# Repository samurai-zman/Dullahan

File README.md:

# Dullahan
A portable "Headless" modular multiport multitool, designed to emphasize adaptability for electronic measurements.

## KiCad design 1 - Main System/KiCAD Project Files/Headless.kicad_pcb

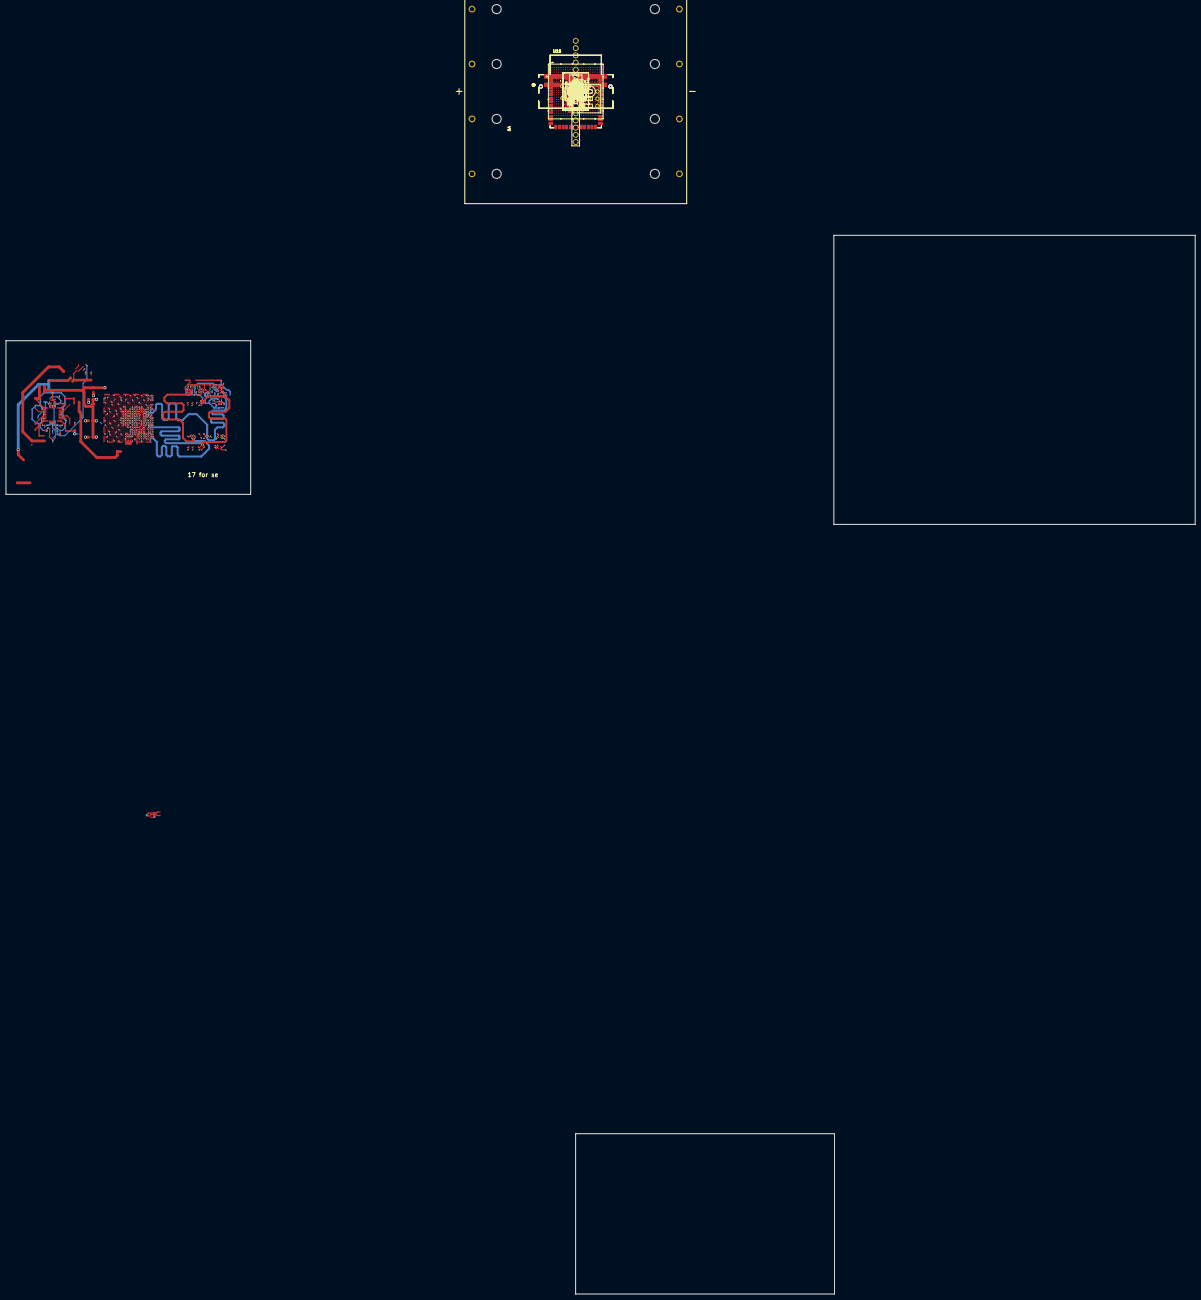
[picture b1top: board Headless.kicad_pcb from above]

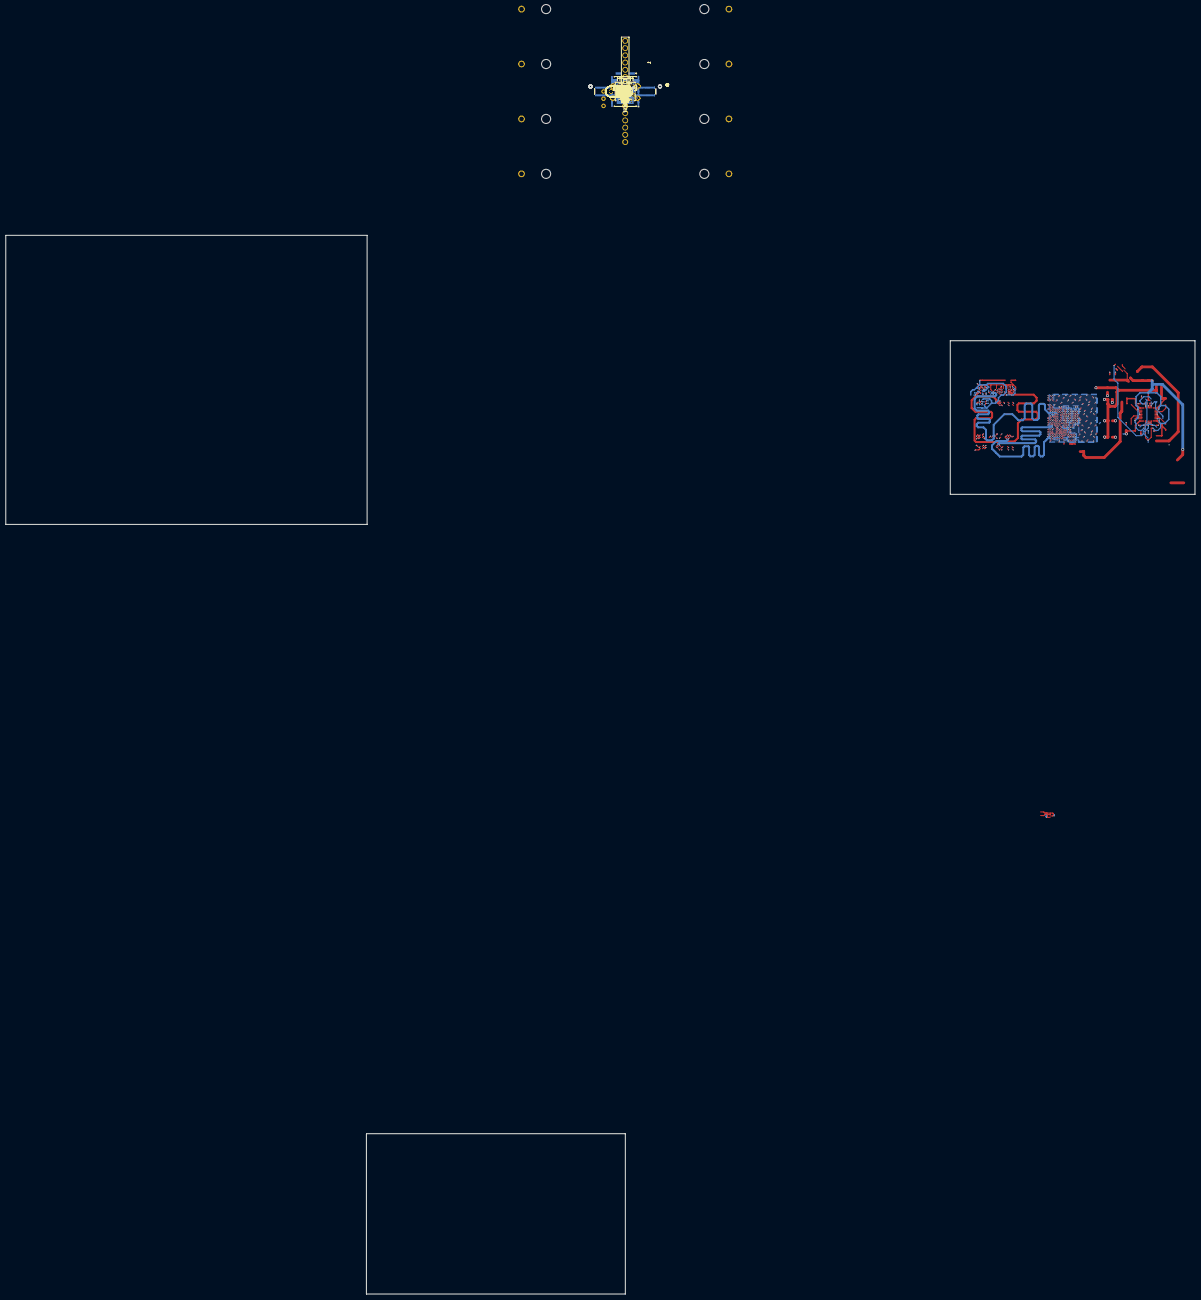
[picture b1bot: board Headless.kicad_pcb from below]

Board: 6 copper layers, 660 parts (243 on the bottom side), 589 nets.

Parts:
BT1: BK-18650-PC8; BAT_BK-18650-PC8
C1, C4, C5, C8, C10, C14, C15, C16, C17, C20, C23, C31, C152, C246, C253: 22uF; C_0805
C2, C3, C32, C35, C160, C162, C164, C166, C168, C237, C249, C285, C286: 1uF; C_0805
C6, C7, C11, C12: 220nF; C_0603
C9, C13, C79, C80, C82, C84, C85, C88, C89, C92, C95, C98, C99, C110, C111, C112, C113, C114, C115, C116, C117, C124, C125, C126, C127, C128, C129, C130, C131, C137, C138, C139, C140, C141, C142, C144, C146: 470nF; C_0402
C18: 47pF; C_0805
C19: 18pF; C_0805
C21, C22, C24, C25, C73, C74, C75: 2.2uF; C_0805_2012Metric
C26, C28, C29, C30, C33, C34, C36, C37, C38, C39, C40, C41, C42, C47, C50, C53, C54, C102, C103, C149, C153, C154, C155, C157, C158, C169, C170, C171, C181, C182, C184, C238, C248, C255: 10uF; C_0805
C27: 33pF; C_0805
C43, C44, C45, C46, C59, C60, C61, C62, C183, C240, C241, C245, C264, C272, C274, C275, C279, C280, C281, C282, C283: 100nF; C_0402
C48, C49, C51, C52, C55, C56, C57, C58: 220pF; C_0805
C63, C64, C65, C66, C68, C72, C100, C151, C161, C163, C165, C167, C172, C173, C175, C250, C265, C267, C268: 100nF; C_0805
C67, C69, C70, C71, C174, C176, C177, C178: 1nF; C_0402
C76: 330uF; C_0603
C77, C78, C81, C87, C91, C94, C97, C106, C107, C108, C109, C120, C121, C122, C123, C134, C135, C136, C145, C266, C269, C270, C271, C273, C276, C277, C278, C284: 4.7uF; C_0402
C83, C96, C133, C143: 100uF; C_0603
C86, C90, C93, C104, C105, C118, C119, C132, C147, C148: 47uF; C_0603
C101, C150, C156, C159: 2.2uF; C_0402
C179, C180, C185, C186, C187, C188, C189, C190, C191, C192, C193, C194, C195, C196, C197, C198, C199, C200, C201, C202, C203, C204, C205, C206, C207, C208, C209, C210, C211, C212, C213, C214, C215, C216, C217, C218, C219, C220, C221, C222, C223, C224, C225, C226, C227, C228, C229, C230, C231, C232, C233, C234, C235, C236: 47nF; C_0402
C242, C243, C244: 10uF; C_0402
C247, C251, C252, C254: 4.7uF; C_0805
D1, D54, D55, D56: PRTR5V0U2X; SOT-143R_Handsoldering
D2, D3, D4, D5, D6, D22, D23, D24, D25, D26, D27, D28, D29, D30, D31, D32, D33, D34, D35, D36, D37, D38, D39, D40, D41, D42, D43, D44, D45, D46, D47, D48, D49, D50, D52, D57, D58, D59, D60, D61, D62, D63, D64, D65, D66, D67, D75, D76, D77, D78, D79, D80, D81, D82, D83: D; D_0805_2012Metric_Pad1.15x1.40mm_HandSolder
D7, D17, D18, D19: BAT60A; D_SOD-323
D8, D9, D10, D11, D12, D13, D14, D20, D21: Blue; LED_0603_1608Metric_Blue
D15: BSTAT; LED_0603
D16: BOK; LED_0603
D51, D53: Blue; D_0805
FB1: FB_0603
IC1, IC2, IC3, IC4: AP22966DC8-7; AP22966DC87
IC5: TMUXHS221FRSWR
IC6, IC7: MAX77857CEWB+; BGA35C40P7X5_283X203X69
IC8, IC9: IS43TR16640C-125JBL; BGA96C80P9X16_900X1300X120
IC11: USB3320C-EZK-TR; QFN50P500X500X100-33N-D
IC12: MIC2097-2YMT-TR; SON50P160X160X60-7N-D
J1, J2, J15: Connector, USB-TYPE-C-16P; TYPE-C-SMD_HX-TYPE-C-16PIN
J3: PinSocket_01x03_P2.54mm_Vertical_SMD; PinSocket_1x03_P2.54mm_Vertical
J4, J7, J8, J9: G97R22312HR; CONN_G97R22xx2HR_AMP
J5: JTAGHDR_RPi; PinHeader_01x08_P2.54mm_Vertical_THT_D1.4mm
J6: JTAGHDR_FPGA; PinHeader_01x08_P2.54mm_Vertical_THT_D1.4mm
J10: TP Module L; JST_1x06_P1.0mm_Horizontal_SMD
J11: TP Module R; JST_1x06_P1.0mm_Horizontal_SMD
J12, J13: DF40C-100DP-0.4V_51_; DF40C100DP04V51
J14: USB_B_Micro; USB_Micro-B_Amphenol_10103594-0001LF_Horizontal
J18: PinHeader_01x01_P2.54mm_Vertical_THT_D1mm
JP3, JP4: Jumper_2_Bridged; Jumper_2_NC_Trace
L1, L21: 1.5uH; Inductor_4.7x4.7mm
L2, L3, L4, L5: 1.0uH; 0805
L6, L11: 120 Ohm; C_0603_1608Metric
L7: 3.3uH; 0806_Polarized
L10: 30 Ohm; C_0603_1608Metric
L12: 0.47uH; Inductor_4.7x4.7mm
Q4: 2N7002; SOT-23
Q5, Q6: T2N7002AK; SOT-23
R1, R2, R4, R8, R37, R38, R42, R43, R44, R82, R83, R84, R85, R86, R87, R115: 10kΩ; R_0402
R3, R6: 510kΩ; R_0402
R5: 200Ω; R_0402
R7: 422Ω; R_0402
R9, R11, R116, R141: 5.1kΩ; R_0805
R10, R18, R35: 1kΩ; R_0805
R12: 5.1Ω; R_0805
R13, R14: 2.2kΩ; R_0805
R15, R16, R119: 10kΩ; R_0805
R17, R19, R23, R59, R124, R126: 12kΩ; R_0402
R20: 47kΩ; R_0805
R21, R22, R25, R28, R29, R30, R45, R118: 330Ω; R_0805
R24, R47, R54, R55, R57, R103, R104, R105, R136, R142, R143, R144: 4.7kΩ; R_0402
R26, R46, R102: 100Ω; R_0402
R27, R39, R40, R41, R71, R74, R80, R81, R98: 0Ω; R_0402
R31, R33, R36: 20kΩ; R_0805
R32: 24kΩ; R_0805
R34: 68kΩ; R_0805
R48, R49, R50, R51, R52, R53, R66, R67, R68, R70, R73, R99, R100, R122, R137: 1kΩ; R_0402
R56: 24.9Ω; R_0402
R58, R77, R140: 510Ω; R_0402
R60, R89, R91, R93, R95, R97, R123: 100kΩ; R_0402
R61, R62, R63, R64, R65, R69, R72: 20kΩ; R_0402
R75, R76, R78, R79, R125, R138: 22Ω; R_0402
R88, R90, R92, R94, R96: 1MΩ; R_0402
R101, R107, R108, R109, R110, R111, R112, R113, R127, R128, R129, R130, R131, R132, R133, R134, R135, R145, R146, R147, R148, R149, R150: 49.9Ω; R_0402
R114, R121: 240Ω; R_0402
R117: 10kΩ; C_0805
R120: 330Ω; C_0805
R139: 8.2kΩ; R_0402
RV1, RV2, RV3, RV4: CG0402MLU-3.3G; VARC1005X41N
S1, S2, S3, S4, S39, S41: Tactile Button, 160gf; SW_TS-1088-AR02016
S5, S6, S7, S8, S9, S10, S11, S12, S13, S14, S15, S16, S17, S18, S19, S20, S21, S22, S23, S24, S25, S26, S27, S28, S29, S30, S31, S32, S33, S34, S35, S36, S37, S38, S40, S45, S46, S47, S48, S49, S50, S51, S52, S53, S54, S55, S62, S63, S64, S65, S66, S67, S68, S69, S70: Tactile Button, 160gf; SW-SMD_4P-L5.1-W5.1-P3.70-LS6.5-TL-2
SW1: SW_DIP_x03; SW_DIP_SPSTx03_Slide_9.78x9.8mm_W7.62mm_P2.54mm
SW2: SPDT_Slide_PTH_11.6x4.0mm; Slide_SPDT_PTH_11.6x4.0mm
TH1: Thermistor_NTC; R_1206
TP6, TP7: TestPoint_Alt; TestPoint-1.0mm
U1: MAX20029BATIA/V+; 21-0140AK_T2855&plus_5_MXM-L
U2, U4, U5, U6, U8, U9: LD39200PU33R; SON95P300X300X100-7N
U3, U18, U30: STTH1002CB-TR; DPAK_STM-L
U7: ADS7830; TSSOP-16_4.4x5mm_P0.65mm
U10, U11: ESP32-S3-WROOM-1-N4; XCVR_ESP32-S3-WROOM-1-N4
U12, U13, U14, U15, U16, U35, U36, U37: ACS711xEXLT-15AB; Allegro_QFN-12-10-1EP_3x3mm_P0.5mm
U17: XC7Z020-1CLG484C; CLG484_XIL-L
U19: MAX77789EWX+T; 21-100639_W362K2&plus_1_ADI-L
U20, U22, U24, U26, U28: TPS2592xx; VSON-10-1EP_3x3mm_P0.5mm_EP1.65x2.4mm_ThermalVias
U21: PCF8574AT; SOIC-16W_7.5x10.3mm_P1.27mm
U23, U29, U31, U32, U33, U34, U38, U39, U40: DSS1NB32A223Q91A; DSS1NB32A223Q91A_MUR
U25: BD3539FVM-TR; MSOP8_ROM
U27: W25Q128JVS; SOIC-8_5.3x5.3mm_P1.27mm
U41: RTL8211EG-VB-CG; QFN-64-1EP_9x9mm_P0.5mm_EP3.8x3.8mm
Y1: ASDMB-xxxMHz; Oscillator_SMD_Abracon_ASDMB-4Pin_2.5x2.0mm
Y2: ASDMB-13MHz; Oscillator_SMD_Abracon_ASDMB-4Pin_2.5x2.0mm

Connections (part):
+0V675: C203.1, C204.1, C205.1, C206.1, C207.1, C208.1, C209.1, C210.1, C211.1, C212.1, C246.1, C247.1, R101.1, R107.1, R108.1, R109.1, R110.1, R111.1, R112.1, R113.1, R127.1, R128.1, R129.1, R130.1, R131.1, R132.1, R133.1, R134.1, R135.1, R145.1, R146.1, R147.1, R148.1, R149.1, R150.1, U25.3 (VTTS), U25.8 (VTT)
+0V675_REF: C251.1, U17.H7 (PS_DDR_VREF0_502), U17.P7 (PS_DDR_VREF1_502), U25.4 (VREF)
+1V0ETH: C278.1, C279.1, C280.1, C281.1, C282.1, L7.2, U41.7 (AVDD10), U41.13 (AVDD10), U41.59 (AVDD10)
+1V0FPGA: C4.1, C5.1, C16.1, C76.1, C77.1, C78.1, C79.1, C80.1, C81.1, C82.1, C83.1, C84.1, C85.1, C133.1, C135.1, C137.1, C139.1, C141.1, L2.1, U1.28 (OUTS1), U17.G8 (VCCPINT), U17.H9 (VCCPINT), U17.H11 (VCCBRAM), U17.J8 (VCCPINT), U17.J10 (VCCBRAM), U17.J12 (VCCINT), U17.J14 (VCCINT), U17.K13 (VCCINT), U17.L8 (VCCPINT), U17.L14 (VCCINT), U17.M13 (VCCINT), U17.N8 (VCCPINT), U17.N14 (VCCINT), U17.P13 (VCCINT), U17.R8 (VCCPINT), U17.R14 (VCCINT)
+1V8FPGA: C19.1, C44.1, C86.1, C87.1, C88.1, C89.1, C93.1, C94.1, C95.1, C99.1, C143.1, C145.1, C146.1, C148.1, C265.1, C266.1, C267.1, C268.1, IC11.14 (REFSEL2), IC11.28 (VDD18_1), IC11.30 (VDD18_2), IC11.32 (VDDIO), L11.2, R17.1, R19.2, R23.2, R36.1, R136.2, R137.1, U17.A10 (VCCO_MIO1_501), U17.B13 (VCCO_MIO1_501), U17.D9 (VCCO_MIO1_501), U17.E12 (VCCO_MIO1_501), U17.G9 (VCCBATT_0), U17.K9 (VCCPAUX), U17.K11 (VCCADC_0), U17.L10 (VCCAUX), U17.M9 (VCCPAUX), U17.N10 (VCCAUX), U17.P9 (VCCPAUX), U17.P11 (VCCAUX), U17.R10 (VCCAUX), U17.T9 (VCCPAUX), Y2.4 (VDD)
+1V35FPGA: C18.1, C104.1, C106.1, C108.1, C110.1, C112.1, C114.1, C116.1, C179.1, C180.1, C185.1, C186.1, C187.1, C188.1, C189.1, C190.1, C191.1, C192.1, C193.1, C194.1, C195.1, C196.1, C197.1, C198.1, C199.1, C200.1, C201.1, C202.1, C214.1, C215.1, C216.1, C217.1, C218.1, C219.1, C220.1, C221.1, C222.1, C223.1, C224.1, C225.1, C226.1, C227.1, C228.1, C229.1, C230.1, C231.1, C232.1, C233.1, C234.1, C236.1, IC8.A1 (VDDQ_1), IC8.A8 (VDDQ_2), IC8.B2 (VDD_1), IC8.C1 (VDDQ_3), IC8.C9 (VDDQ_4), IC8.D2 (VDDQ_5), IC8.D9 (VDD_2), IC8.E9 (VDDQ_6), IC8.F1 (VDDQ_7), IC8.G7 (VDD_3), IC8.H1 (VREFDQ), IC8.H2 (VDDQ_8), IC8.H9 (VDDQ_9), IC8.K2 (VDD_4), IC8.K8 (VDD_5), IC8.N1 (VDD_6), IC8.N9 (VDD_7), IC8.R1 (VDD_8), IC8.R9 (VDD_9), IC9.A1 (VDDQ_1), IC9.A8 (VDDQ_2), IC9.B2 (VDD_1), IC9.C1 (VDDQ_3), IC9.C9 (VDDQ_4), IC9.D2 (VDDQ_5), IC9.D9 (VDD_2), IC9.E9 (VDDQ_6), IC9.F1 (VDDQ_7), IC9.G7 (VDD_3), IC9.H1 (VREFDQ)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
+3V3ETH: C275.1, C276.1, FB1.2, U41.10 (AVDD33), U41.60 (AVDD33)
+3V3FPGA: C27.1, C90.1, C91.1, C92.1, C105.1, C107.1, C109.1, C111.1, C113.1, C115.1, C117.1, C118.1, C119.1, C120.1, C121.1, C122.1, C123.1, C124.1, C125.1, C126.1, C127.1, C128.1, C129.1, C130.1, C131.1, C132.1, C134.1, C136.1, C138.1, C140.1, C142.1, C144.1, C147.1, C250.1, C264.1, C272.1, C273.1, C274.1, C277.1, C283.1, C284.1, FB1.1, IC11.20 (VDD33), IC11.21 (VBAT), J6.8, R21.1, R33.1, R54.2, R55.2, R57.2, R58.1, R62.2, R71.1, R74.2, R77.1, R103.2, R104.2, R105.2, R126.1, R142.1, R144.1, SW1.4, SW1.5, SW1.6, U17.A20 (VCCO_35), U17.AA10 (VCCO_13), U17.AA20 (VCCO_33), U17.AB3 (VCCO_13), U17.AB13 (VCCO_33), U17.B3 (VCCO_MIO0_500), U17.C6 (VCCO_MIO0_500), U17.C16 (VCCO_35), U17.D19 (VCCO_35), U17.E22 (VCCO_35), U17.F15 (VCCO_35), U17.G18 (VCCO_35), U17.H21 (VCCO_35), U17.K17 (VCCO_34), U17.L20 (VCCO_34), U17.N16 (VCCO_34)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
+3V3JTAG: C62.1, C184.1, C237.1, C238.1, J5.8, R45.1, R115.1, U8.1 (OUT), U8.2 (SENSE), U10.2 (3V3)
+3V3KEB: C63.1, C248.1, C249.1, C255.1, J10.1, J11.1, R117.1, R120.1, U9.1 (OUT), U9.2 (SENSE), U11.2 (3V3)
+5V0JTAG: C103.1, C149.1, C181.1, C285.1, C286.1, D1.4 (VCC), D15.2 (A), D16.2 (A), D56.4 (VCC), IC5.9 (VCC), J15.A9B4 (VBUS), J15.B9A4 (VBUS), L12.1, U3.1, U3.2, U8.5 (EN), U8.6 (IN), U18.1, U18.2, U19.D4 (SYS), U19.D5 (SYS), U19.D6 (SYS), U30.1, U30.2
+5VB: R48.2, R49.2, R50.2, R51.2, R52.2, R53.2, R99.2, R100.2
+5VM: C14.1, C15.1, C64.1, C65.1, C66.1, C68.1, C72.1, C172.1, C173.1, C175.1, C242.1, C244.1, D7.2 (A), D17.2 (A), D18.2 (A), D19.2 (A), IC7.D4 (OUT_1), IC7.E1 (FB), IC7.E4 (OUT_2), IC7.E5 (OUT_3), IC7.E6 (OUT_4), R12.2, R13.1, R14.1, R15.1, R16.1, R119.1, U12.10 (VCC), U13.10 (VCC), U14.10 (VCC), U15.10 (VCC), U16.10 (VCC), U21.16 (VDD), U35.10 (VCC), U36.10 (VCC), U37.10 (VCC)
+5VU: C269.1, IC12.6 (VIN)
+VIOB: C150.1, R2.1, R82.1, R83.1, U19.F4 (VDD)
+VIOM: C13.1, IC7.A2 (VIO), R8.1, R86.1, R87.1
+VIOPI: C9.1, IC6.A2 (VIO), R4.1, R84.1, R85.1
/3V3 Regulator Supplies/3M1: U37.1 (IP+), U40.3
/3V3 Regulator Supplies/3M2: U36.1 (IP+), U39.3
/3V3 Regulator Supplies/3M3: U35.1 (IP+), U38.3
/3V3 Regulator Supplies/3M4: U16.1 (IP+), U34.3
/3V3 Regulator Supplies/5M1: U15.1 (IP+), U33.3
/3V3 Regulator Supplies/5M2: U14.1 (IP+), U32.3
/3V3 Regulator Supplies/5M3: U13.1 (IP+), U31.3
/3V3 Regulator Supplies/5M4: U12.1 (IP+), U29.3
/3V3 Regulator Supplies/5VM1: C53.1, C160.1, C171.1, IC1.1 (VIN1), IC1.5 (VIN2), R98.1, U20.6 (OUT), U20.7 (OUT), U20.8 (OUT)
/3V3 Regulator Supplies/5VM2: C50.1, C164.1, C170.1, IC2.1 (VIN1), IC2.5 (VIN2), R81.1, U24.6 (OUT), U24.7 (OUT), U24.8 (OUT)
/3V3 Regulator Supplies/5VM3: C47.1, C166.1, C169.1, IC3.1 (VIN1), IC3.5 (VIN2), R80.1, U26.6 (OUT), U26.7 (OUT), U26.8 (OUT)
/3V3 Regulator Supplies/5VM4: C36.1, C54.1, C168.1, IC4.1 (VIN1), IC4.5 (VIN2), R27.1, U28.6 (OUT), U28.7 (OUT), U28.8 (OUT)
/3V3 Regulator Supplies/M1_3VEN: IC1.4 (EN2), U21.5 (P1)
/3V3 Regulator Supplies/M1_5VEN: IC1.2 (EN1), U21.11 (P6)
/3V3 Regulator Supplies/M1_PG: U2.4 (PG), U10.26 (IO45)
/3V3 Regulator Supplies/M2_3VEN: IC2.4 (EN2), U21.7 (P3)
/3V3 Regulator Supplies/M2_5VEN: IC2.2 (EN1), U21.9 (P4)
/3V3 Regulator Supplies/M2_PG: U4.4 (PG), U10.16 (IO46)
/3V3 Regulator Supplies/M3_3VEN: IC3.4 (EN2), U21.10 (P5)
/3V3 Regulator Supplies/M3_5VEN: IC3.2 (EN1), U21.6 (P2)
/3V3 Regulator Supplies/M3_PG: U5.4 (PG), U10.24 (IO47)
/3V3 Regulator Supplies/M4_3VEN: IC4.4 (EN2), U21.12 (P7)
/3V3 Regulator Supplies/M4_5VEN: IC4.2 (EN1), U21.4 (P0)
/3V3 Regulator Supplies/M4_PG: U6.4 (PG), U10.25 (IO48)
/5V Boost Supplies/5VM_INT: IC7.C2 (POKB/_INTB), R87.2, R119.2, U10.23 (IO21), U21.13 (~INT)
/5V Boost Supplies/5VM_SCL: IC7.A1 (SCL), R14.2, R16.2, R86.2, U7.14 (SCL), U10.11 (IO18), U21.15 (SDA)
/5V Boost Supplies/5VM_SDA: IC7.B1 (SDA), R8.2, R13.2, R15.2, U7.15 (SDA), U10.10 (IO17), U21.14 (SCL)
/5V Boost Supplies/5VP_INT: IC6.C2 (POKB/_INTB), R83.2, R84.2, U10.30 (IO37), U19.B1 (INTB)
/5V Boost Supplies/5VP_SCL: IC6.A1 (SCL), R82.2, R85.2, U10.34 (IO41), U19.D1 (SCL)
/5V Boost Supplies/5VP_SDA: IC6.B1 (SDA), R2.2, R4.2, U10.33 (IO40), U19.C1 (SDA)
/FPGA Power Distro/FPGA_PG: C75.2, Q4.1 (G), R44.2, R124.1, U1.23 (PG4)
/FPGA/FPGA CFG and PWR/BOOT0: R63.1, R66.1, SW1.3
/FPGA/FPGA CFG and PWR/BOOT1: R65.1, R67.1, SW1.1
/FPGA/FPGA CFG and PWR/BOOT2: R64.1, R68.1, SW1.2
/FPGA/FPGA CFG and PWR/CLK: R56.1, Y1.3 (Out)
/FPGA/FPGA CFG and PWR/DONE: Q6.1 (G), U17.T12 (DONE_0)
/FPGA/FPGA CFG and PWR/FPGA_TCK: J6.3, R79.1, R104.1, RV1.1
/FPGA/FPGA CFG and PWR/FPGA_TDI: J6.1, R75.1, R103.1, RV4.1
/FPGA/FPGA CFG and PWR/FPGA_TDO: J6.2, R76.1, RV3.1
/FPGA/FPGA CFG and PWR/FPGA_TMS: J6.4, R78.1, R105.1, RV2.1
/FPGA/FPGA CFG and PWR/PS_LED: R59.1, R60.2, U17.G6 (PS_MIO0_500)
/FPGA/FPGA CFG and PWR/QBOO_CLK_BM4: R72.2, R125.1, U17.A4 (PS_MIO6_500)
/FPGA/FPGA CFG and PWR/QBOO_CS: R126.2, U17.A1 (PS_MIO1_500), U27.1 (~CS)
/FPGA/FPGA CFG and PWR/QBOO_D0_BM3: R69.2, U17.A2 (PS_MIO2_500), U27.5 (DI/IO_{0})
/FPGA/FPGA CFG and PWR/QBOO_D1_BM1: R65.2, U17.F6 (PS_MIO3_500), U27.2 (DO/IO_{1})
/FPGA/FPGA CFG and PWR/QBOO_D2_BM2: R64.2, U17.E4 (PS_MIO4_500), U27.3 (~WP/IO_{2})
/FPGA/FPGA CFG and PWR/QBOO_D3_BM0: R63.2, U17.A3 (PS_MIO5_500), U27.7 (~HOLD/~RESET/IO_{3})
/FPGA/FPGA CFG and PWR/QBOO_VM0: R61.2, U17.D5 (PS_MIO7_500)
/FPGA/FPGA CFG and PWR/QBOO_VM1: R62.1, U17.E5 (PS_MIO8_500)
/FPGA/FPGA CFG and PWR/nINIT: R55.1, U17.T14 (INIT_B_0)
/FPGA/FPGA CFG and PWR/nPROGRAM: R54.1, S1.2 (B), U17.T11 (PROGRAM_B_0)
/FPGA/FPGA CFG and PWR/nSRST: C43.1, J6.5, R17.2, S3.2 (B), U17.C9 (PS_SRST_B_501)
/FPGA/FPGA DDR/DDR1_DQL0: IC8.E3 (DQL0), U17.F1 (PS_DDR_DQ7_502)
/FPGA/FPGA DDR/DDR1_DQL1: IC8.F7 (DQL1), U17.K1 (PS_DDR_DQ13_502)
/FPGA/FPGA DDR/DDR1_DQL2: IC8.F2 (DQL2), U17.E3 (PS_DDR_DQ4_502)
/FPGA/FPGA DDR/DDR1_DQL3: IC8.F8 (DQL3), U17.L3 (PS_DDR_DQ12_502)
/FPGA/FPGA DDR/DDR1_DQL4: IC8.H3 (DQL4), U17.F2 (PS_DDR_DQ6_502)
/FPGA/FPGA DDR/DDR1_DQL5: IC8.H8 (DQL5), U17.L2 (PS_DDR_DQ11_502)
/FPGA/FPGA DDR/DDR1_DQL6: IC8.G2 (DQL6), U17.B2 (PS_DDR_DQ2_502)
/FPGA/FPGA DDR/DDR1_DQL7: IC8.H7 (DQL7), U17.L1 (PS_DDR_DQ10_502)
/FPGA/FPGA DDR/DDR1_DQU0: IC8.D7 (DQU0), U17.K3 (PS_DDR_DQ15_502)
/FPGA/FPGA DDR/DDR1_DQU1: IC8.C3 (DQU1), U17.E1 (PS_DDR_DQ5_502)
/FPGA/FPGA DDR/DDR1_DQU2: IC8.C8 (DQU2), U17.G1 (PS_DDR_DQ9_502)
/FPGA/FPGA DDR/DDR1_DQU3: IC8.C2 (DQU3), U17.C3 (PS_DDR_DQ1_502)
/FPGA/FPGA DDR/DDR1_DQU4: IC8.A7 (DQU4), U17.J1 (PS_DDR_DQ14_502)
/FPGA/FPGA DDR/DDR1_DQU5: IC8.A2 (DQU5), U17.D3 (PS_DDR_DQ3_502)
/FPGA/FPGA DDR/DDR1_DQU6: IC8.B8 (DQU6), U17.G2 (PS_DDR_DQ8_502)
/FPGA/FPGA DDR/DDR1_DQU7: IC8.A3 (DQU7), U17.D1 (PS_DDR_DQ0_502)
/FPGA/FPGA DDR/DDR2_DQL0: IC9.E3 (DQL0), U17.T2 (PS_DDR_DQ21_502)
/FPGA/FPGA DDR/DDR2_DQL1: IC9.F7 (DQL1), U17.Y3 (PS_DDR_DQ29_502)
/FPGA/FPGA DDR/DDR2_DQL2: IC9.F2 (DQL2), U17.R3 (PS_DDR_DQ20_502)
/FPGA/FPGA DDR/DDR2_DQL3: IC9.F8 (DQL3), U17.Y1 (PS_DDR_DQ31_502)
/FPGA/FPGA DDR/DDR2_DQL4: IC9.H3 (DQL4), U17.T3 (PS_DDR_DQ17_502)
/FPGA/FPGA DDR/DDR2_DQL5: IC9.H8 (DQL5), U17.AA1 (PS_DDR_DQ26_502)
/FPGA/FPGA DDR/DDR2_DQL6: IC9.G2 (DQL6), U17.M1 (PS_DDR_DQ16_502)
/FPGA/FPGA DDR/DDR2_DQL7: IC9.H7 (DQL7), U17.AA3 (PS_DDR_DQ24_502)
/FPGA/FPGA DDR/DDR2_DQU0: IC9.D7 (DQU0), U17.W1 (PS_DDR_DQ28_502)
/FPGA/FPGA DDR/DDR2_DQU1: IC9.C3 (DQU1), U17.R1 (PS_DDR_DQ23_502)
/FPGA/FPGA DDR/DDR2_DQU2: IC9.C8 (DQU2), U17.U1 (PS_DDR_DQ25_502)
/FPGA/FPGA DDR/DDR2_DQU3: IC9.C2 (DQU3), U17.M2 (PS_DDR_DQ22_502)
/FPGA/FPGA DDR/DDR2_DQU4: IC9.A7 (DQU4), U17.W3 (PS_DDR_DQ30_502)
/FPGA/FPGA DDR/DDR2_DQU5: IC9.A2 (DQU5), U17.N3 (PS_DDR_DQ18_502)
/FPGA/FPGA DDR/DDR2_DQU6: IC9.B8 (DQU6), U17.U2 (PS_DDR_DQ27_502)
/FPGA/FPGA DDR/DDR2_DQU7: IC9.A3 (DQU7), U17.T1 (PS_DDR_DQ19_502)
/FPGA/FPGA DDR/DDR_A0: IC8.N3 (A0), IC9.N3 (A0), R127.2, U17.M4 (PS_DDR_A0_502)
/FPGA/FPGA DDR/DDR_A1: IC8.P7 (A1), IC9.P7 (A1), R128.2, U17.M5 (PS_DDR_A1_502)
/FPGA/FPGA DDR/DDR_A2: IC8.P3 (A2), IC9.P3 (A2), R129.2, U17.K4 (PS_DDR_A2_502)
/FPGA/FPGA DDR/DDR_A3: IC8.N2 (A3), IC9.N2 (A3), R130.2, U17.L4 (PS_DDR_A3_502)
/FPGA/FPGA DDR/DDR_A4: IC8.P8 (A4), IC9.P8 (A4), R131.2, U17.K6 (PS_DDR_A4_502)
/FPGA/FPGA DDR/DDR_A5: IC8.P2 (A5), IC9.P2 (A5), R132.2, U17.K5 (PS_DDR_A5_502)
/FPGA/FPGA DDR/DDR_A6: IC8.R8 (A6), IC9.R8 (A6), R133.2, U17.J7 (PS_DDR_A6_502)
/FPGA/FPGA DDR/DDR_A7: IC8.R2 (A7), IC9.R2 (A7), R134.2, U17.J6 (PS_DDR_A7_502)
/FPGA/FPGA DDR/DDR_A8: IC8.T8 (A8), IC9.T8 (A8), R135.2, U17.J5 (PS_DDR_A8_502)
/FPGA/FPGA DDR/DDR_A9: IC8.R3 (A9), IC9.R3 (A9), R145.2, U17.H5 (PS_DDR_A9_502)
/FPGA/FPGA DDR/DDR_A10: IC8.L7 (A10/AP), IC9.L7 (A10/AP), R146.2, U17.J3 (PS_DDR_A10_502)
/FPGA/FPGA DDR/DDR_A11: IC8.R7 (A11), IC9.R7 (A11), R147.2, U17.G5 (PS_DDR_A11_502)
/FPGA/FPGA DDR/DDR_A12: IC8.N7 (A12/BC#), IC9.N7 (A12/BC#), R148.2, U17.H4 (PS_DDR_A12_502)
/FPGA/FPGA DDR/DDR_A13: IC8.T3 (NC(A13)), IC9.T3 (NC(A13)), R149.2, U17.F4 (PS_DDR_A13_502)
/FPGA/FPGA DDR/DDR_A14: IC8.T7 (NC(A14)), IC9.T7 (NC(A14)), R150.2, U17.G4 (PS_DDR_A14_502)
/FPGA/FPGA DDR/DDR_BA0: IC8.M2 (BA0), IC9.M2 (BA0), R111.2, U17.L7 (PS_DDR_BA0_502)
/FPGA/FPGA DDR/DDR_BA1: IC8.N8 (BA1), IC9.N8 (BA1), R112.2, U17.L6 (PS_DDR_BA1_502)
/FPGA/FPGA DDR/DDR_BA2: IC8.M3 (BA2), IC9.M3 (BA2), R113.2, U17.M6 (PS_DDR_BA2_502)
/FPGA/FPGA DDR/DDR_CAS: IC8.K3 (CAS#), IC9.K3 (CAS#), R108.2, U17.P3 (PS_DDR_CAS_B_502)
/FPGA/FPGA DDR/DDR_CKE: IC8.K9 (CKE), IC9.K9 (CKE), U17.V3 (PS_DDR_CKE_502)
/FPGA/FPGA DDR/DDR_CKN: IC8.K7 (CK#), IC9.K7 (CK#), R102.1, U17.N5 (PS_DDR_CKN_502)
/FPGA/FPGA DDR/DDR_CKP: IC8.J7 (CK), IC9.J7 (CK), R102.2, U17.N4 (PS_DDR_CKP_502)
/FPGA/FPGA DDR/DDR_CS: IC8.L2 (CS#), IC9.L2 (CS#), R107.2, U17.P6 (PS_DDR_CS_B_502)
/FPGA/FPGA DDR/DDR_DM0: IC8.D3 (DMU), IC9.D3 (DMU), U17.B1 (PS_DDR_DM0_502)
/FPGA/FPGA DDR/DDR_DM1: IC8.E7 (DML), IC9.E7 (DML), U17.H3 (PS_DDR_DM1_502)
/FPGA/FPGA DDR/DDR_ODT: IC8.K1 (ODT), IC9.K1 (ODT), R101.2, U17.P5 (PS_DDR_ODT_502)
/FPGA/FPGA DDR/DDR_RAS: IC8.J3 (RAS#), IC9.J3 (RAS#), R109.2, U17.R5 (PS_DDR_RAS_B_502)
/FPGA/FPGA DDR/DDR_WE: IC8.L3 (WE#), IC9.L3 (WE#), R110.2, U17.R4 (PS_DDR_WE_B_502)
/FPGA/FPGA DDR/DDR_ZQ: IC8.L8 (ZQ), IC9.L8 (ZQ), R114.1, R121.2
/FPGA/FPGA DDR/DDR_nRST: IC8.T2 (RESET#), IC9.T2 (RESET#), R47.1, U17.F3 (PS_DDR_DRST_B_502)
/FPGA/FPGA DDR/DQSL_N: IC8.G3 (DQSL#), IC9.G3 (DQSL#), U17.J2 (PS_DDR_DQS_N1_502)
/FPGA/FPGA DDR/DQSL_P: IC8.F3 (DQSL), IC9.F3 (DQSL), U17.H2 (PS_DDR_DQS_P1_502)
/FPGA/FPGA DDR/DQSU_N: IC8.B7 (DQSU#), IC9.B7 (DQSU#), U17.D2 (PS_DDR_DQS_N0_502)
/FPGA/FPGA DDR/DQSU_P: IC8.C7 (DQSU), IC9.C7 (DQSU), U17.C2 (PS_DDR_DQS_P0_502)
/FPGA/FPGA ETHER/E_LED0: R142.2, U41.50 (LED0/PHY_AD0)
/FPGA/FPGA ETHER/E_LED1: R143.2, U41.51 (LED1/PHY_AD1)
/FPGA/FPGA ETHER/E_LED2: R144.2, U41.52 (LED2)
/FPGA/FPGA USB/HSDN: D55.3 (I/O2), IC11.19 (DM), J14.2 (D-)
/FPGA/FPGA USB/HSDP: D55.2 (I/O1), IC11.18 (DP), J14.3 (D+)
/FPGA/FPGA USB/U_HSID: IC11.23 (ID), J14.4 (ID)
/FPGA/FPGA USB/U_NRST: IC11.27 (RESETB), R137.2
/FPGA/LP_1: J12.1, U17.B7 (PS_MIO24_501)
/FPGA/LP_3: J12.3, U17.A6 (PS_MIO13_500)
/FPGA/LP_4: J12.4, U17.E9 (PS_MIO17_501)
/FPGA/LP_5: J12.5, U17.A7 (PS_MIO18_501)
/FPGA/LP_6: J12.6, U17.D6 (PS_MIO16_501)
/FPGA/LP_7: J12.7, U17.A8 (PS_MIO20_501)
/FPGA/LP_8: J12.8, U17.C5 (PS_MIO12_500)
/FPGA/LP_9: J12.9, U17.E8 (PS_MIO29_501)
/FPGA/LP_10: J12.10, U17.E6 (PS_MIO15_500)
/FPGA/LP_11: J12.11, U17.D8 (PS_MIO42_501)
/FPGA/LP_13: J12.13, U17.C13 (PS_MIO39_501)
/FPGA/LP_14: J12.14, U17.B6 (PS_MIO14_500)
/FPGA/LP_15: J12.15, U17.B12 (PS_MIO34_501)
/FPGA/LP_16: J12.16, U17.B4 (PS_MIO11_500)
/FPGA/LP_17: J12.17, U17.C12 (PS_MIO53_501)
/FPGA/LP_18: J12.18, U17.D7 (PS_MIO27_501)
/FPGA/LP_19: J12.19, U17.D12 (PS_MIO46_501)
/FPGA/LP_20: J12.20, U17.C7 (PS_MIO32_501)
/FPGA/LP_21: J12.21, U17.E10 (PS_MIO19_501)
/FPGA/LP_23: J12.23, U17.C8 (PS_MIO41_501)
/FPGA/LP_25: J12.25, U17.C10 (PS_MIO51_501)
/FPGA/LP_26: J12.26, U17.G7 (PS_MIO10_500)
/FPGA/LP_27: J12.27, U17.A9 (PS_MIO36_501)
/FPGA/LP_28: J12.28, U17.F11 (PS_MIO21_501)
/FPGA/LP_29: J12.29, U17.B9 (PS_MIO45_501)
/FPGA/LP_30: J12.30, U17.F12 (PS_MIO25_501)
/FPGA/LP_31: J12.31, U17.D10 (PS_MIO52_501)
/FPGA/LP_33: J12.33, U17.D11 (PS_MIO48_501)
/FPGA/LP_35: J12.35, U17.F13 (PS_MIO38_501)
/FPGA/LP_37: J12.37, U17.E14 (PS_MIO40_501)
/FPGA/LP_38: J12.38, U17.F9 (PS_MIO31_501)
/FPGA/LP_39: J12.39, U17.C14 (PS_MIO49_501)
/FPGA/LP_40: J12.40, U17.E11 (PS_MIO23_501)
/FPGA/LP_41: J12.41, U17.B14 (PS_MIO37_501)
/FPGA/LP_42: J12.42, U17.E13 (PS_MIO44_501)
/FPGA/LP_43: J12.43, U17.A14 (PS_MIO22_501)
/FPGA/LP_44: J12.44, U17.B10 (PS_MIO47_501)
/FPGA/LP_45: J12.45, U17.B15 (IO_L7N_T1_AD2N_35), U17.D22 (IO_L16P_T2_35)
/FPGA/LP_46: J12.46, U17.G13 (PS_MIO33_501)
/FPGA/LP_47: J12.47, U17.F14 (PS_MIO35_501)
/FPGA/LP_48: J12.48, U17.B11 (PS_MIO43_501)
/FPGA/LP_49: J12.49, U17.A16 (IO_L9P_T1_DQS_AD3P_35)
/FPGA/LP_50: J12.50, U17.A11 (PS_MIO30_501)
/FPGA/LP_51: J12.51, U17.B17 (IO_L8N_T1_AD10N_35)
/FPGA/LP_52: J12.52, U17.D13 (PS_MIO50_501)
/FPGA/LP_53: J12.53, U17.A17 (IO_L9N_T1_DQS_AD3N_35)
/FPGA/LP_54: J12.54, U17.A13 (PS_MIO26_501)
/FPGA/LP_55: J12.55, U17.G15 (IO_L4P_T0_35)
/FPGA/LP_56: J12.56, U17.A12 (PS_MIO28_501)
/FPGA/LP_57: J12.57, U17.C18 (IO_L11N_T1_SRCC_35)
/FPGA/LP_58: J12.58, U17.F17 (IO_L6N_T0_VREF_35)
/FPGA/LP_59: J12.59, U17.A18 (IO_L10P_T1_AD11P_35)
/FPGA/LP_60: J12.60, U17.E15 (IO_L3P_T0_DQS_AD1P_35)
/FPGA/LP_61: J12.61, U17.D16 (IO_L2P_T0_AD8P_35)
/FPGA/LP_62: J12.62, U17.D15 (IO_L3N_T0_DQS_AD1N_35)
/FPGA/LP_63: J12.63, U17.D17 (IO_L2N_T0_AD8N_35)
/FPGA/LP_64: J12.64, U17.C15 (IO_L7P_T1_AD2P_35)
/FPGA/LP_65: J12.65, U17.F16 (IO_L1P_T0_AD0P_35)
/FPGA/LP_66: J12.66, U17.B16 (IO_L8P_T1_AD10P_35)
/FPGA/LP_67: J12.67, U17.E18 (IO_L5N_T0_AD9N_35)
/FPGA/LP_68: J12.68, U17.E16 (IO_L1N_T0_AD0N_35)
/FPGA/LP_69: J12.69, U17.G19 (IO_L20P_T3_AD6P_35)
/FPGA/LP_70: J12.70, U17.C17 (IO_L11P_T1_SRCC_35)
/FPGA/LP_71: J12.71, U17.E19 (IO_L21P_T3_DQS_AD14P_35)
/FPGA/LP_72: J12.72, U17.F18 (IO_L5P_T0_AD9P_35)
/FPGA/LP_73: J12.73, U17.F19 (IO_L20N_T3_AD6N_35)
/FPGA/LP_74: J12.74, U17.D18 (IO_L12P_T1_MRCC_35)
/FPGA/LP_75: J12.75, U17.G17 (IO_L6P_T0_35)
/FPGA/LP_76: J12.76, U17.H17 (IO_0_35)
/FPGA/LP_77: J12.77, U17.G16 (IO_L4N_T0_35)
/FPGA/LP_78: J12.78, U17.C20 (IO_L14N_T2_AD4N_SRCC_35)
/FPGA/LP_79: J12.79, U17.B19 (IO_L13P_T2_MRCC_35)
/FPGA/LP_80: J12.80, U17.G20 (IO_L22P_T3_AD7P_35)
/FPGA/LP_81: J12.81, U17.A19 (IO_L10N_T1_AD11N_35)
/FPGA/LP_82: J12.82, U17.D20 (IO_L14P_T2_AD4P_SRCC_35)
/FPGA/LP_83: J12.83, U17.C19 (IO_L12N_T1_MRCC_35)
/FPGA/LP_84: J12.84, U17.E20 (IO_L21N_T3_DQS_AD14N_35)
/FPGA/LP_85: J12.85, U17.B20 (IO_L13N_T2_MRCC_35)
/FPGA/LP_86: J12.86, U17.H18 (IO_25_35)
/FPGA/LP_87: J12.87, U17.A21 (IO_L15P_T2_DQS_AD12P_35)
/FPGA/LP_88: J12.88, U17.F21 (IO_L23P_T3_35)
/FPGA/LP_89: J12.89, U17.B21 (IO_L18P_T2_AD13P_35)
/FPGA/LP_90: J12.90, U17.H19 (IO_L19P_T3_35)
/FPGA/LP_91: J12.91, U17.A22 (IO_L15N_T2_DQS_AD12N_35)
/FPGA/LP_92: J12.92, U17.F22 (IO_L23N_T3_35)
/FPGA/LP_93: J12.93, U17.B22 (IO_L18N_T2_AD13N_35)
/FPGA/LP_94: J12.94, U17.G21 (IO_L22N_T3_AD7N_35)
/FPGA/LP_95: J12.95, U17.C22 (IO_L16N_T2_35)
/FPGA/LP_96: J12.96, U17.H20 (IO_L19N_T3_VREF_35)
/FPGA/LP_97: J12.97, U17.D21 (IO_L17N_T2_AD5N_35)
/FPGA/LP_98: J12.98, U17.G22 (IO_L24N_T3_AD15N_35)
/FPGA/LP_99: J12.99, U17.E21 (IO_L17P_T2_AD5P_35)
/FPGA/LP_100: J12.100, U17.H22 (IO_L24P_T3_AD15P_35)
/FPGA/UP_1: J13.2, U17.T21 (IO_L1P_T0_33)
/FPGA/UP_2: J13.1, U17.T22 (IO_L2P_T0_33)
/FPGA/UP_3: J13.4, U17.U21 (IO_L1N_T0_33)
/FPGA/UP_4: J13.3, U17.U22 (IO_L2N_T0_33)
/FPGA/UP_5: J13.6, U17.V20 (IO_L5N_T0_33)
/FPGA/UP_6: J13.5, U17.V22 (IO_L3P_T0_DQS_33)
/FPGA/UP_7: J13.8, U17.W21 (IO_L4N_T0_33)
/FPGA/UP_8: J13.7, U17.W22 (IO_L3N_T0_DQS_33)
/FPGA/UP_9: J13.10, U17.Y21 (IO_L9N_T1_DQS_33)
/FPGA/UP_10: J13.9, U17.AA22 (IO_L7P_T1_33)
/FPGA/UP_11: J13.12, U17.AB22 (IO_L7N_T1_33)
/FPGA/UP_12: J13.11, U17.AA21 (IO_L8P_T1_33)
/FPGA/UP_13: J13.14, U17.AB21 (IO_L8N_T1_33)
/FPGA/UP_14: J13.13, U17.AB20 (IO_L10N_T1_33)
/FPGA/UP_15: J13.16, U17.AA19 (IO_L11N_T1_SRCC_33)
/FPGA/UP_16: J13.15, U17.AA18 (IO_L12N_T1_MRCC_33)
/FPGA/UP_17: J13.18, U17.AB17 (IO_L17N_T2_33)
/FPGA/UP_18: J13.17, U17.AA17 (IO_L17P_T2_33)
/FPGA/UP_19: J13.20, U17.AB16 (IO_L18N_T2_33)
/FPGA/UP_20: J13.19, U17.AA16 (IO_L18P_T2_33)
/FPGA/UP_21: J13.22, U17.AB15 (IO_L24N_T3_33)
/FPGA/UP_22: J13.21, U17.AA14 (IO_L22N_T3_33)
/FPGA/UP_23: J13.24, U17.AB14 (IO_L24P_T3_33)
/FPGA/UP_24: J13.23, U17.AB19 (IO_L10P_T1_33)
/FPGA/UP_25: J13.26, U17.W20 (IO_L4P_T0_33)
/FPGA/UP_26: J13.25, U17.Y14 (IO_L22P_T3_33)
/FPGA/UP_27: J13.28, U17.Y19 (IO_L11P_T1_SRCC_33)
/FPGA/UP_28: J13.27, U17.V18 (IO_L6P_T0_33)
/FPGA/UP_29: J13.30, U17.W17 (IO_L13P_T2_MRCC_33)
/FPGA/UP_30: J13.29, U17.U20 (IO_L5P_T0_33)
/FPGA/UP_31: J13.32, U17.W16 (IO_L14P_T2_SRCC_33)
/FPGA/UP_32: J13.31, U17.U19 (IO_0_33)
/FPGA/UP_33: J13.34, U17.Y15 (IO_L21N_T3_DQS_33)
/FPGA/UP_34: J13.33, U17.U17 (IO_L16P_T2_33)
/FPGA/UP_35: J13.36, U17.V15 (IO_L19N_T3_VREF_33)
/FPGA/UP_36: J13.35, U17.W13 (IO_L20N_T3_33)
/FPGA/UP_37: J13.38, U17.V19 (IO_L6N_T0_VREF_33)
/FPGA/UP_38: J13.37, U17.V17 (IO_L16N_T2_33)
/FPGA/UP_39: J13.40, U17.Y20 (IO_L9P_T1_DQS_33)
/FPGA/UP_40: J13.39, U17.V13 (IO_L20P_T3_33)
/FPGA/UP_41: J13.42, U17.Y18 (IO_L12P_T1_MRCC_33)
/FPGA/UP_42: J13.41, U17.V14 (IO_L19P_T3_33)
/FPGA/UP_43: J13.44, U17.Y16 (IO_L14N_T2_SRCC_33)
/FPGA/UP_44: J13.43, U17.AB12 (IO_L7N_T1_13)
/FPGA/UP_45: J13.46, U17.W18 (IO_L13N_T2_MRCC_33)
/FPGA/UP_46: J13.45, U17.AA12 (IO_L7P_T1_13)
/FPGA/UP_47: J13.48, U17.W15 (IO_L21P_T3_DQS_33)
/FPGA/UP_48: J13.47, U17.AB11 (IO_L8N_T1_13)
/FPGA/UP_49: J13.50, U17.Y13 (IO_L23P_T3_33)
/FPGA/UP_50: J13.49, U17.AA11 (IO_L8P_T1_13)
/FPGA/UP_51: J13.52, U17.AA13 (IO_L23N_T3_33)
/FPGA/UP_52: J13.51, U17.AB10 (IO_L9P_T1_DQS_13)
/FPGA/UP_53: J13.54, U17.U16 (IO_L15N_T2_DQS_33)
/FPGA/UP_54: J13.53, U17.AA9 (IO_L11P_T1_SRCC_13)
/FPGA/UP_55: J13.56, U17.U14 (IO_25_33)
/FPGA/UP_56: J13.55, U17.AB9 (IO_L9N_T1_DQS_13)
/FPGA/UP_57: J13.58, U17.U15 (IO_L15P_T2_DQS_33)
/FPGA/UP_58: J13.57, U17.AA8 (IO_L11N_T1_SRCC_13)
/FPGA/UP_59: J13.60, U17.Y11 (IO_L10P_T1_13)
/FPGA/UP_60: J13.59, U17.AB7 (IO_L17P_T2_13)
/FPGA/UP_61: J13.62, U17.W11 (IO_L3P_T0_DQS_13)
/FPGA/UP_62: J13.61, U17.AB6 (IO_L17N_T2_13)
/FPGA/UP_63: J13.64, U17.Y9 (IO_L12P_T1_MRCC_13)
/FPGA/UP_64: J13.63, U17.AB5 (IO_L16P_T2_13)
/FPGA/UP_65: J13.66, U17.Y10 (IO_L10N_T1_13)
/FPGA/UP_66: J13.65, U17.AA4 (IO_L18N_T2_13)
/FPGA/UP_67: J13.68, U17.Y8 (IO_L12N_T1_MRCC_13)
/FPGA/UP_68: J13.67, U17.U12 (IO_L5P_T0_13)
/FPGA/UP_69: J13.70, U17.W10 (IO_L3N_T0_DQS_13)
/FPGA/UP_70: J13.69, U17.U11 (IO_L5N_T0_13)
/FPGA/UP_71: J13.72, U17.V9 (IO_L1N_T0_13)
/FPGA/UP_72: J13.71, U17.V10 (IO_L1P_T0_13)
/FPGA/UP_73: J13.74, U17.Y6 (IO_L13P_T2_MRCC_13)
/FPGA/UP_74: J13.73, U17.U10 (IO_L6P_T0_13)
/FPGA/UP_75: J13.76, U17.AA7 (IO_L14P_T2_SRCC_13)
/FPGA/UP_76: J13.75, U17.V8 (IO_L2P_T0_13)
/FPGA/UP_77: J13.78, U17.AA6 (IO_L14N_T2_SRCC_13)
/FPGA/UP_78: J13.77, U17.W8 (IO_L2N_T0_13)
/FPGA/UP_79: J13.80, U17.Y5 (IO_L13N_T2_MRCC_13)
/FPGA/UP_80: J13.79, U17.W7 (IO_L23N_T3_13)
/FPGA/UP_81: J13.82, U17.Y4 (IO_L18P_T2_13)
/FPGA/UP_82: J13.81, U17.V7 (IO_L23P_T3_13)
/FPGA/UP_83: J13.84, U17.W6 (IO_L24P_T3_13)
/FPGA/UP_84: J13.83, U17.U9 (IO_L6N_T0_VREF_13)
/FPGA/UP_85: J13.86, U17.V4 (IO_L21N_T3_DQS_13)
/FPGA/UP_86: J13.85, U17.T6 (IO_L19N_T3_VREF_13)
/FPGA/UP_87: J13.88, U17.U7 (IO_25_13)
/FPGA/UP_88: J13.87, U17.W5 (IO_L24N_T3_13)
/FPGA/UP_89: J13.90, U17.U4 (IO_L20N_T3_13)
/FPGA/UP_90: J13.89, U17.V5 (IO_L21P_T3_DQS_13)
/FPGA/UP_91: J13.92, U17.V12 (IO_L4P_T0_13)
/FPGA/UP_92: J13.91, U17.U6 (IO_L22P_T3_13)
/FPGA/UP_93: J13.94, U17.W12 (IO_L4N_T0_13)
/FPGA/UP_94: J13.93, U17.U5 (IO_L22N_T3_13)
/FPGA/UP_95: J13.96, U17.AB4 (IO_L16N_T2_13)
/FPGA/UP_96: J13.95, U17.T4 (IO_L20P_T3_13)
/FPGA/UP_97: J13.98, U17.AB2 (IO_L15P_T2_DQS_13)
/FPGA/UP_98: J13.97, U17.R6 (IO_L19P_T3_13)
/FPGA/UP_99: J13.100, U17.AB1 (IO_L15N_T2_DQS_13)
/FPGA/UP_100: J13.99, U17.R7 (IO_0_13)
/Interface/Interface Controller/CC1: J2.A5 (CC1), R9.1
/Interface/Interface Controller/CC2: J2.B5 (CC2), R11.1
/Interface/Interface Controller/COL0: S5.1 (A), S5.2 (B), S15.1 (A), S15.2 (B), S24.1 (A), S24.2 (B), S31.1 (A), S31.2 (B), U11.6 (IO6)
/Interface/Interface Controller/COL1: S6.1 (A), S6.2 (B), S16.1 (A), S16.2 (B), S25.1 (A), S25.2 (B), S32.1 (A), S32.2 (B), U11.7 (IO7)
/Interface/Interface Controller/COL2: S7.1 (A), S7.2 (B), S17.1 (A), S17.2 (B), S26.1 (A), S26.2 (B), S33.1 (A), S33.2 (B), U11.10 (IO17)
/Interface/Interface Controller/COL3: S8.1 (A), S8.2 (B), S18.1 (A), S18.2 (B), S27.1 (A), S27.2 (B), S34.1 (A), S34.2 (B), U11.11 (IO18)
/Interface/Interface Controller/COL4: S9.1 (A), S9.2 (B), S19.1 (A), S19.2 (B), S28.1 (A), S28.2 (B), S35.1 (A), S35.2 (B), U11.12 (IO8)
/Interface/Interface Controller/COL5: S10.1 (A), S10.2 (B), S20.1 (A), S20.2 (B), S29.1 (A), S29.2 (B), S62.1 (A), S62.2 (B), U11.16 (IO46)
/Interface/Interface Controller/COL6: S11.1 (A), S11.2 (B), S21.1 (A), S21.2 (B), S30.1 (A), S30.2 (B), S63.1 (A), S63.2 (B), U11.17 (IO9)
/Interface/Interface Controller/COL7: S12.1 (A), S12.2 (B), S22.1 (A), S22.2 (B), S36.1 (A), S36.2 (B), S64.1 (A), S64.2 (B), U11.18 (IO10)
/Interface/Interface Controller/COL8: S13.1 (A), S13.2 (B), S23.1 (A), S23.2 (B), S37.1 (A), S37.2 (B), S65.1 (A), S65.2 (B), U11.19 (IO11)
/Interface/Interface Controller/COL9: S14.1 (A), S14.2 (B), S38.1 (A), S38.2 (B), S40.1 (A), S40.2 (B), S66.1 (A), S66.2 (B), U11.20 (IO12)
/Interface/Interface Controller/COL10: S45.1 (A), S45.2 (B), S46.1 (A), S46.2 (B), S47.1 (A), S47.2 (B), S67.1 (A), S67.2 (B), U11.21 (IO13)
/Interface/Interface Controller/COL11: S48.1 (A), S48.2 (B), S49.1 (A), S49.2 (B), S50.1 (A), S50.2 (B), S68.1 (A), S68.2 (B), U11.22 (IO14)
/Interface/Interface Controller/COL12: S51.1 (A), S51.2 (B), S54.1 (A), S54.2 (B), S55.1 (A), S55.2 (B), S69.1 (A), S69.2 (B), U11.23 (IO21)
/Interface/Interface Controller/COL13: S52.1 (A), S52.2 (B), S70.1 (A), S70.2 (B), U11.24 (IO47)
/Interface/Interface Controller/COL14: S53.1 (A), S53.2 (B), U11.25 (IO48)
/Interface/Interface Controller/I2C0_SCL: J10.5, U11.38 (IO2)
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
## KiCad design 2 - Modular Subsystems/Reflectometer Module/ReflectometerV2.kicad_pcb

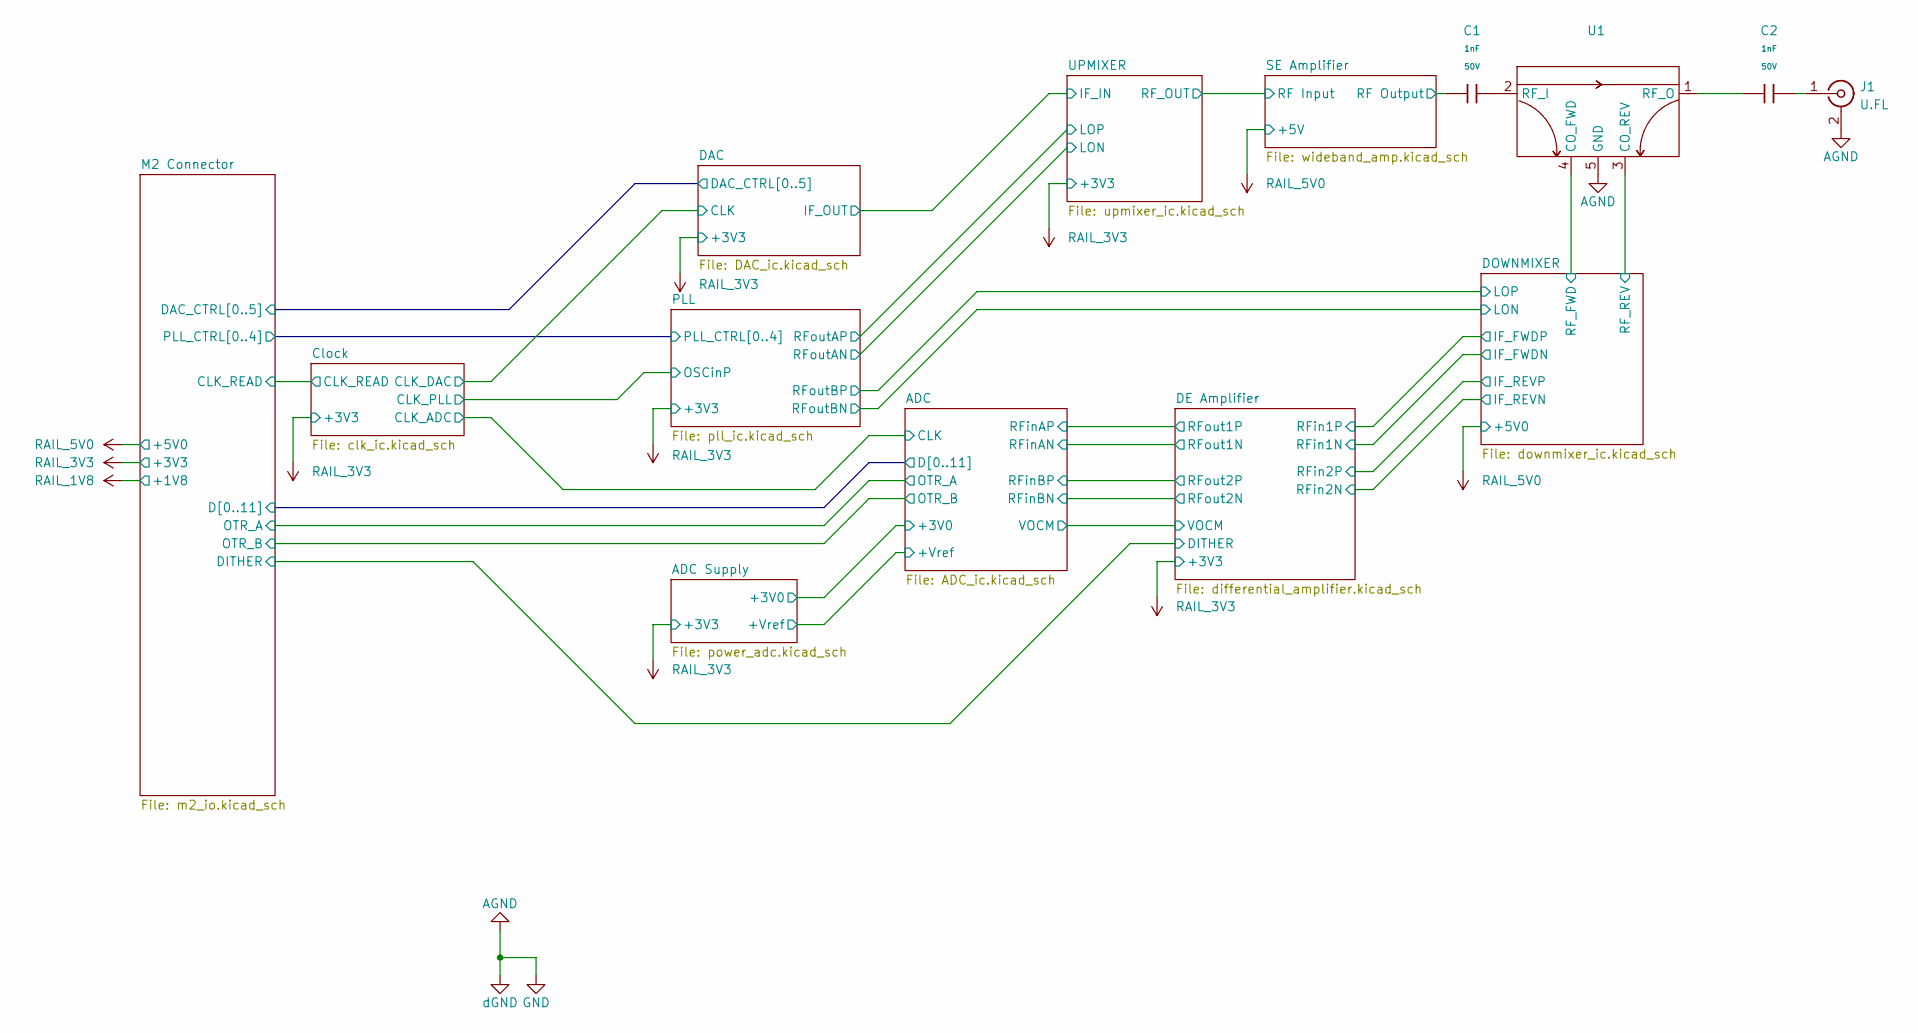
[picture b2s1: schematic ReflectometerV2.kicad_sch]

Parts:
C1, C2: 1nF; C_0402; Voltage Rated 50V; Tolerance ±10%; Part 0402B102K500NT; LCSC C1523
J1: U.FL; SMA_Amphenol_132289_EdgeMount; LCSC C5137195
U1: PL-423Q

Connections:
/DOWNMIXER/RF_FWD: U1.4 (CO_FWD); also elsewhere on the board
/DOWNMIXER/RF_REV: U1.3 (CO_REV); also elsewhere on the board
/SE Amplifier/RF Output: C1.1; also elsewhere on the board
AGND: J1.2 (Ext), U1.5 (GND); also elsewhere on the board
unnamed: C2.2, J1.1 (In)
unnamed: C1.2, U1.2 (RF_I)
unnamed: C2.1, U1.1 (RF_O)
